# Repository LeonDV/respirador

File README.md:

# respirador
Código colaborativo respirador UIS

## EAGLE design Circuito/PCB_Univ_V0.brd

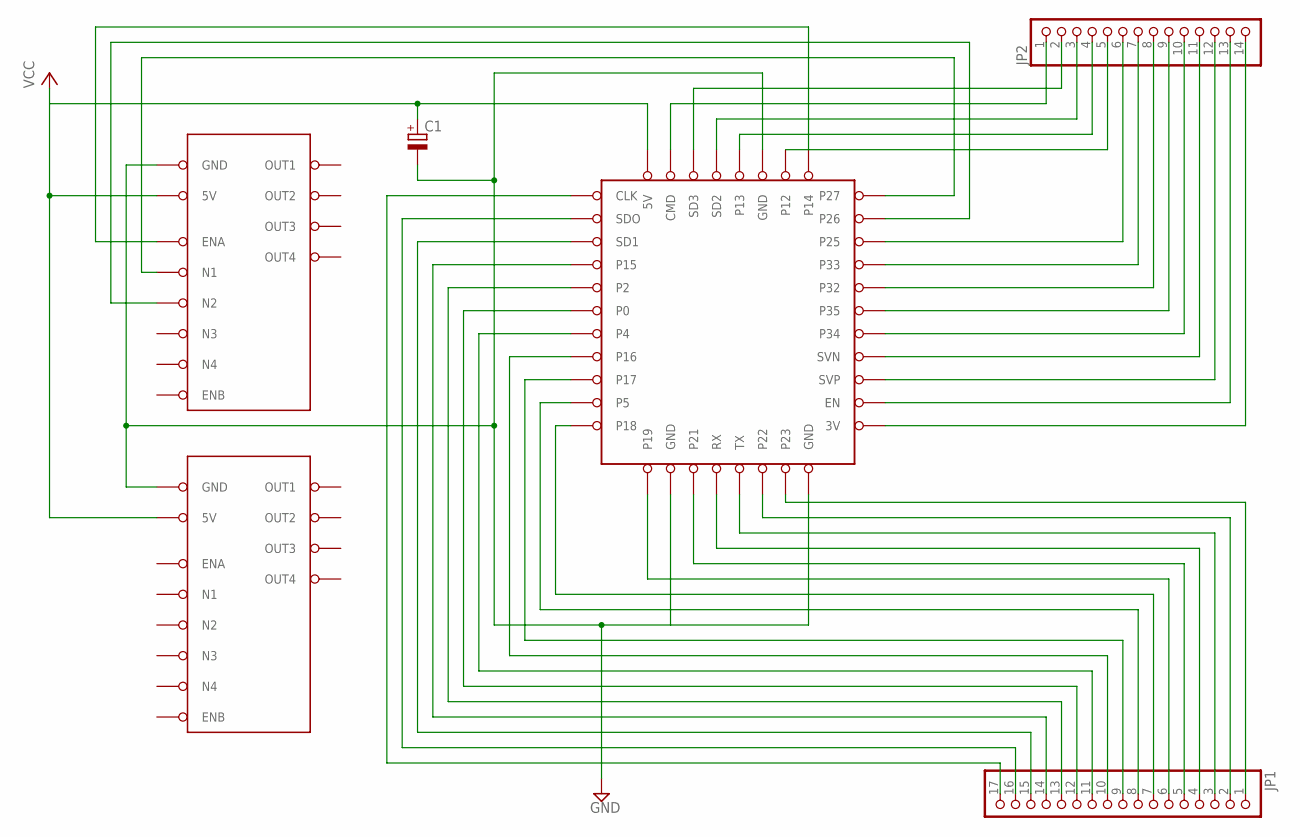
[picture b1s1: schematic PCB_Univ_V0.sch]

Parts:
C1: CPOL-EUE3.5-8; E3,5-8
ESP1: ESP12_MOD; ESP32_MOD
JP1: PINHD-1X17; 1X17
JP2: PINHD-1X14; 1X14
U$1, U$2: DRIVER_MOTOR

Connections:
GND: C1.-, ESP1.P$13 (GND), ESP1.P$19 (GND), ESP1.P$33 (GND), U$1.GND, U$2.GND
unnamed: ESP1.P$30 (P27), U$1.N1
unnamed: ESP1.P$29 (P26), U$1.N2
unnamed: ESP1.P$31 (P14), U$1.ENA
unnamed: ESP1.P$37 (CMD), JP2.1
unnamed: ESP1.P$36 (SD3), JP2.2
unnamed: ESP1.P$35 (SD2), JP2.3
unnamed: ESP1.P$34 (P13), JP2.4
unnamed: ESP1.P$32 (P12), JP2.5
unnamed: ESP1.P$28 (P25), JP2.6
unnamed: ESP1.P$27 (P33), JP2.7
unnamed: ESP1.P$26 (P32), JP2.8
unnamed: ESP1.P$25 (P35), JP2.9
unnamed: ESP1.P$24 (P34), JP2.10
unnamed: ESP1.P$23 (SVN), JP2.11
unnamed: ESP1.P$22 (SVP), JP2.12
unnamed: ESP1.P$21 (EN), JP2.13
unnamed: ESP1.P$20 (3V), JP2.14
unnamed: ESP1.P$18 (P23), JP1.1
unnamed: ESP1.P$17 (P22), JP1.2
unnamed: ESP1.P$16 (TX), JP1.3
unnamed: ESP1.P$15 (RX), JP1.4
unnamed: ESP1.P$14 (P21), JP1.5
unnamed: ESP1.P$12 (P19), JP1.6
unnamed: ESP1.P$11 (P18), JP1.7
unnamed: ESP1.P$10 (P5), JP1.8
unnamed: ESP1.P$9 (P17), JP1.9
unnamed: ESP1.P$8 (P16), JP1.10
unnamed: ESP1.P$7 (P4), JP1.11
unnamed: ESP1.P$6 (P0), JP1.12
unnamed: ESP1.P$5 (P2), JP1.13
unnamed: ESP1.P$4 (P15), JP1.14
unnamed: ESP1.P$3 (SD1), JP1.15
unnamed: ESP1.P$2 (SDO), JP1.16
unnamed: ESP1.P$1 (CLK), JP1.17
VCC: C1.+, ESP1.P$38 (5V), U$1.5V, U$2.5V

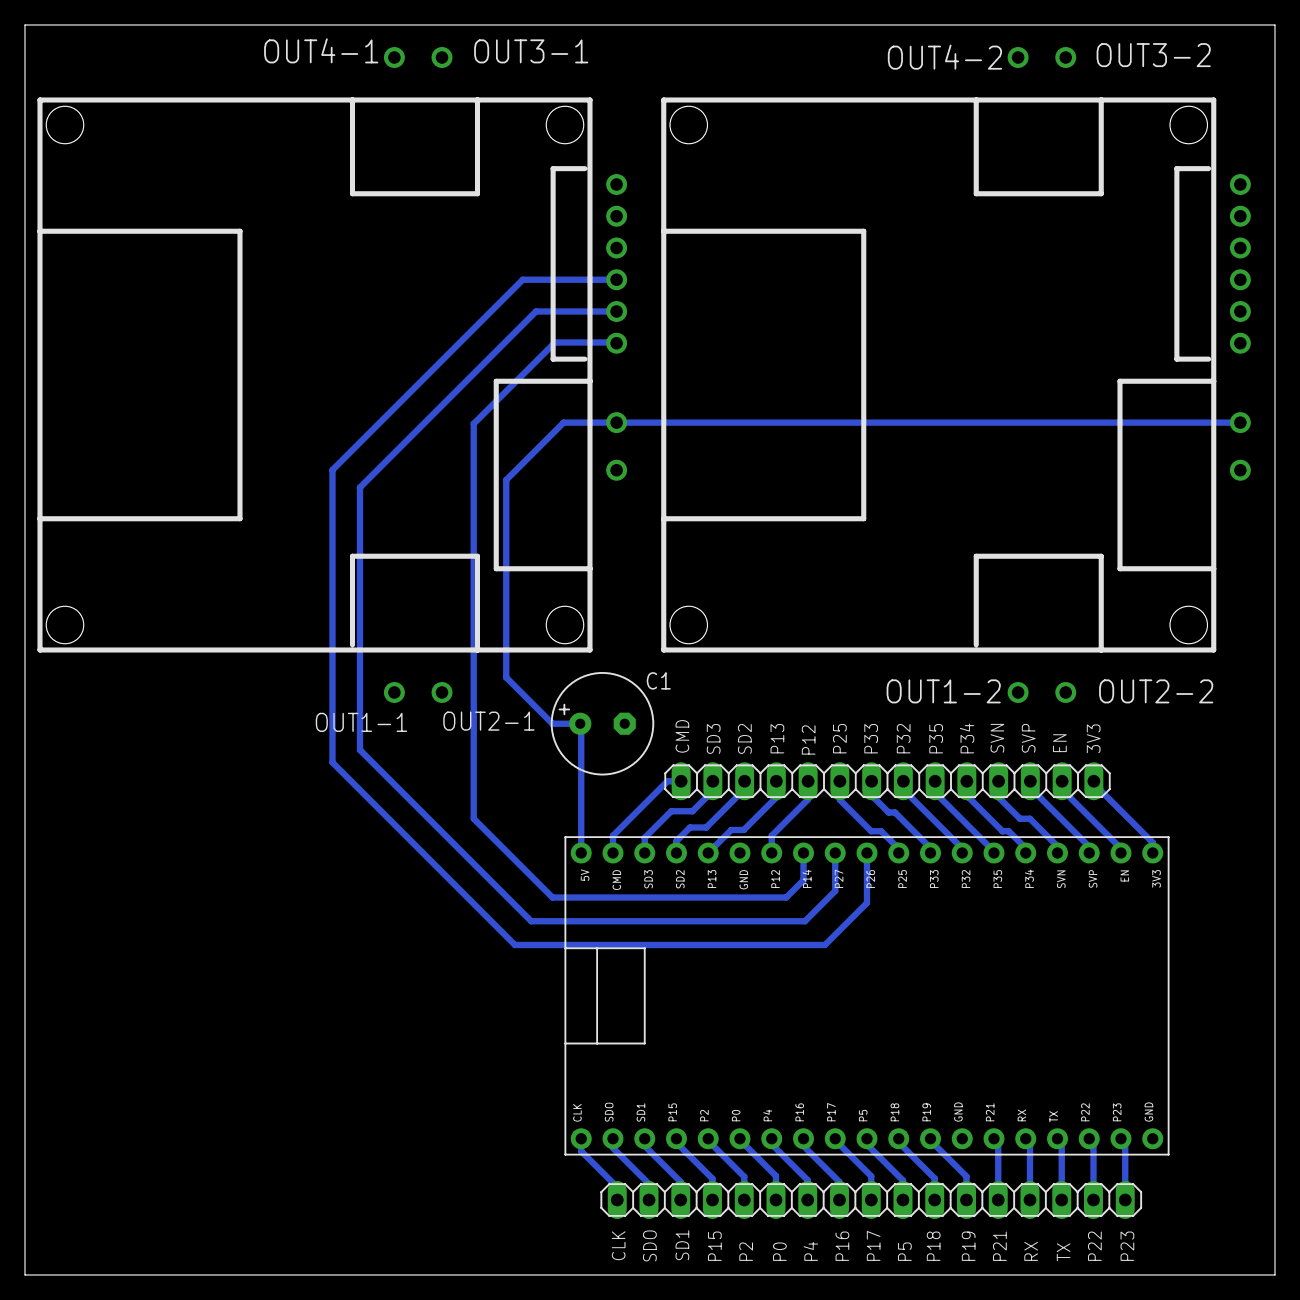
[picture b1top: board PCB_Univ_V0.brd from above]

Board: 2 copper layers, 100.0 x 100.0 mm, 6 parts (0 on the bottom side), 36 nets.

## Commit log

2020-04-21 Carga de archivos inicial
2020-04-21 Modificaciones de descripción
2020-04-21 Código de Oscar Eduardo Perez
2020-04-21 Interfaz Respirador OLED SH1106
2020-05-03 Códigos David Padilla
2020-05-12 Diseño controlador
2020-05-22 Circuito
    Circuito ESP32 y dos Drivers
2020-05-22 Circuito - img
2020-05-22 Circuito V0
2020-05-27 Gerber
